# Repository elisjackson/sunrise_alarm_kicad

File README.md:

# sunrise_alarm_kicad

KiCAD project files for the Sunrise Alarm PCB.

## Folder Structure

- **`hardware/`**  
  Contains all files necessary to open the project in KiCAD.  
  _Note:_ The `footprints/` and `symbols/` folders may need to be manually linked in KiCAD if they are not automatically recognized.

- **`production/`**  
  Includes the Gerber files used to manufacture the PCB. This includes the custom silkscreen artwork layer, which was created using EasyEDA.

- **`artwork/`**  
  Contains the source file used to create the silkscreen artwork.

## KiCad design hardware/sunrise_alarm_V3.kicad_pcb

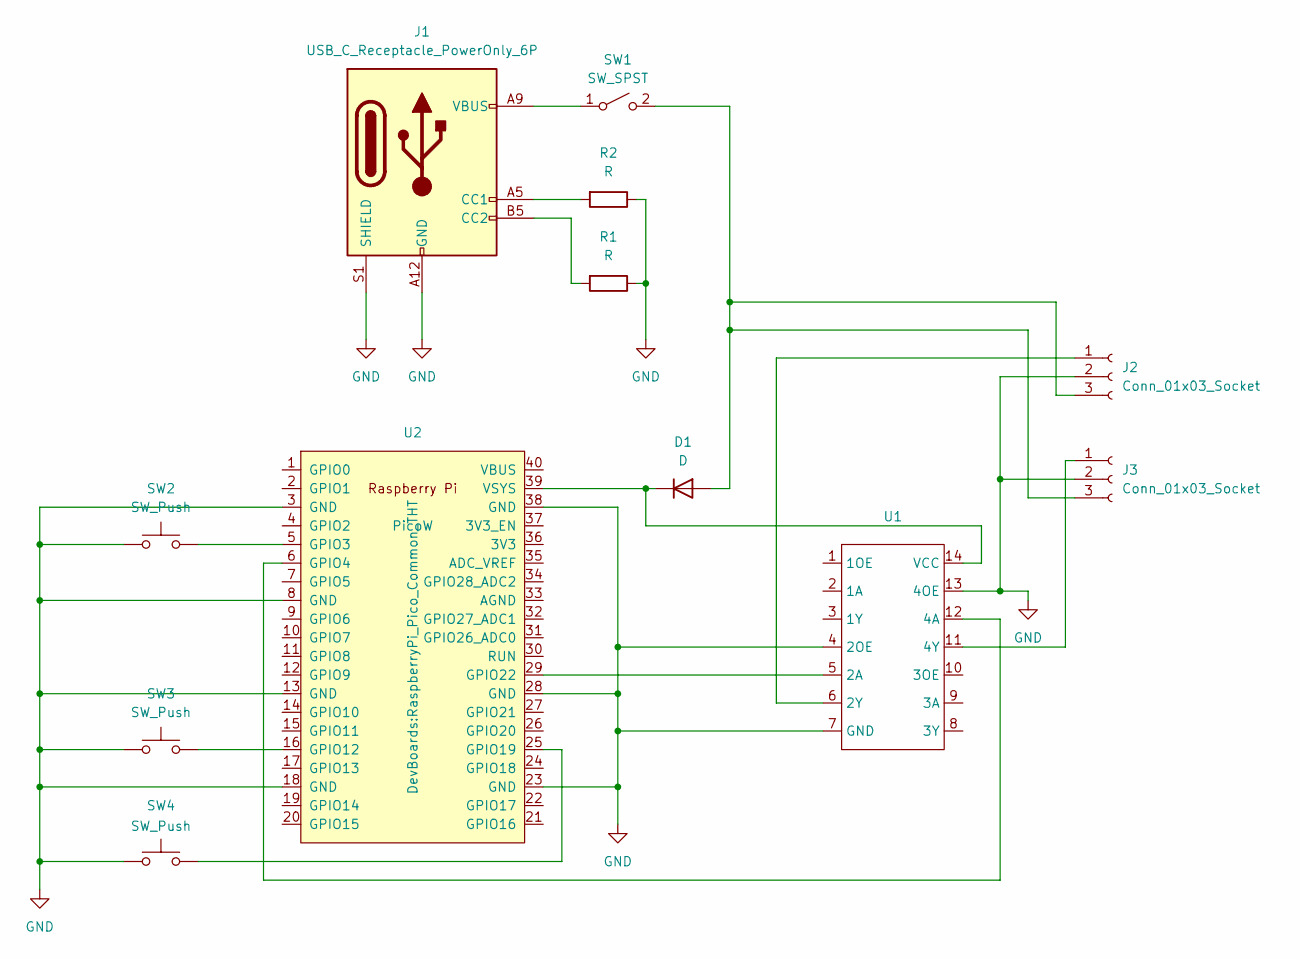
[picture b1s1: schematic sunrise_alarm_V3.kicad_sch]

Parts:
D1: D; D_A-405_P7.62mm_Horizontal
J1: USB_C_Receptacle_PowerOnly_6P; USB_C_Receptacle_GCT_USB4125-xx-x-0190_6P_TopMnt_Horizontal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
J2, J3: Conn_01x03_Socket; JST_XH_S3B-XH-A_1x03_P2.50mm_Horizontal
R1, R2: R; R_Axial_DIN0207_L6.3mm_D2.5mm_P10.16mm_Horizontal
SW1: SW_SPST; SPST_Amazon
SW2, SW3, SW4: SW_Push; SW_PUSH_6mm
U1: DIP-14_W7.62mm
U2: PicoW; RaspberryPi_Pico_Common_THT

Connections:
GND: J1.A12 (GND), J1.B12 (GND), J1.S1 (SHIELD), J2.2, J3.2, R1.1, R2.1, SW2.1, SW3.1, SW4.1, U1.4 (2OE), U1.7 (GND), U1.13 (4OE), U2.3 (GND), U2.8 (GND), U2.13 (GND), U2.18 (GND), U2.23 (GND), U2.28 (GND), U2.38 (GND)
unnamed: D1.2 (A), J2.3, J3.3, SW1.2 (B)
unnamed: D1.1 (K), U1.14 (VCC), U2.39 (VSYS)
unnamed: J1.A5 (CC1), R2.2
unnamed: J1.B5 (CC2), R1.2
unnamed: J2.1, U1.6 (2Y)
unnamed: J3.1, U1.11 (4Y)
unnamed: J1.A9 (VBUS), J1.B9 (VBUS), SW1.1 (A)
unnamed: U1.5 (2A), U2.29 (GPIO22)
unnamed: U1.12 (4A), U2.6 (GPIO4)
unnamed: SW2.2, U2.5 (GPIO3)
unnamed: SW3.2, U2.16 (GPIO12)
unnamed: SW4.2, U2.25 (GPIO19)

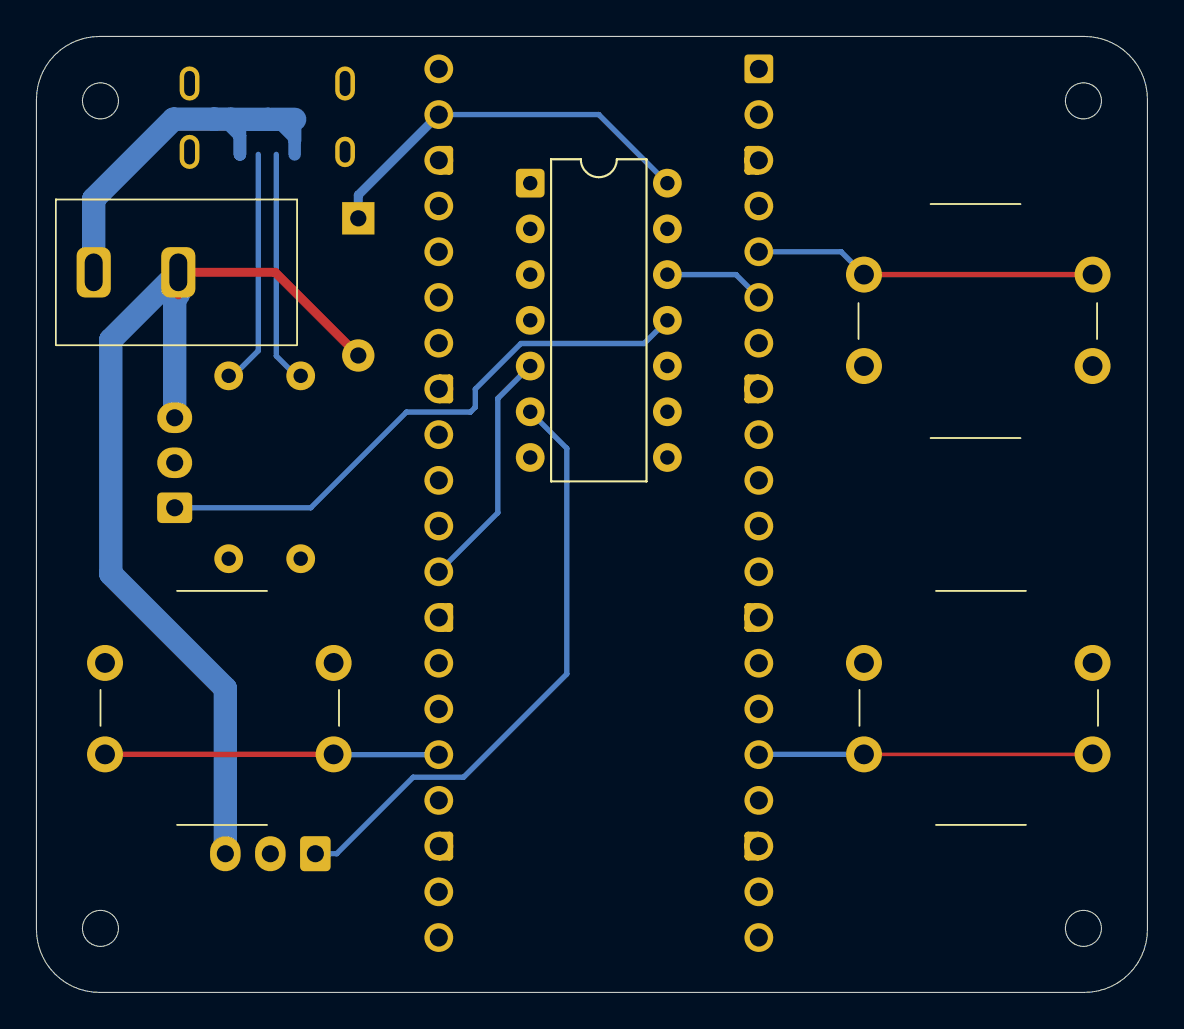
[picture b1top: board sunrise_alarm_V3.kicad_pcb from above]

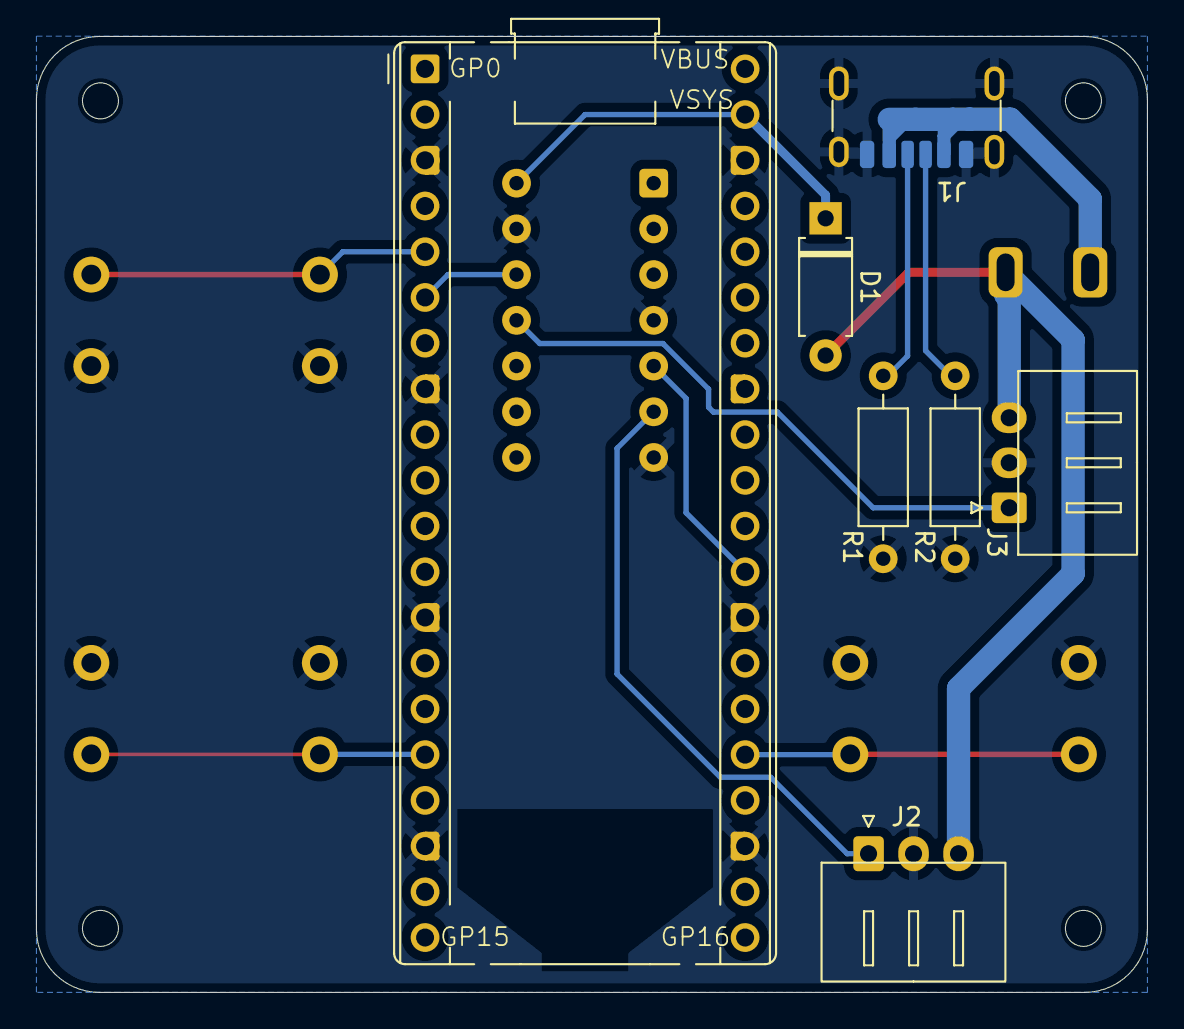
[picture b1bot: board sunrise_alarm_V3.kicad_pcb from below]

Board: 2 copper layers, 61.7 x 53.1 mm, 12 parts (7 on the bottom side), 13 nets.

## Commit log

2025-05-26 add gerber file
